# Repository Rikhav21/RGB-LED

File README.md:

# RGB-LED

## About
This is basically my attempt at making an RGB LED. I hope that I will get at least one red, green, nad blue LED,(If not I have a few), and I wat to try to turn on each LED witha  button, so that I can change the combination of the LEDs on, so tha I can make any color, and I also added a potentiameter, for the intensity for overall brightness, however I would add a poteniameter for each LEDm so that you can make any color. 
## BOM
- LED 1 Red, 1 Blue, and 1 green
- 3 220 Ohm resistors
- 1 PCB
- 3 push buttons
- 1 potentiameter
## Images

## Slack ID
U083L25T929

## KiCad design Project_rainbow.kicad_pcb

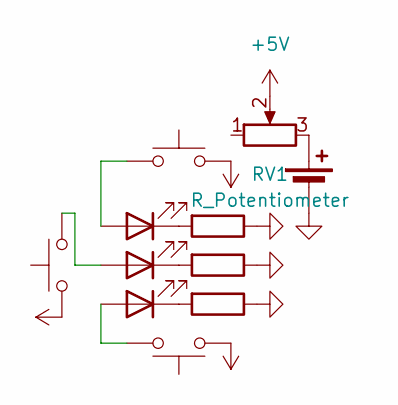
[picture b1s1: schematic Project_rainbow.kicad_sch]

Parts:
BT1: Battery_Cell; BatteryHolder_Keystone_3034_1x20mm
D1, D2, D3: LED; LED_D5.0mm
R1, R2, R3: R; R_Axial_DIN0207_L6.3mm_D2.5mm_P7.62mm_Horizontal
RV1: R_Potentiometer; Potentiometer_Vishay_T73YP_Vertical
SW4, SW5, SW6: SW_Push; SW_PUSH_6mm

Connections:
+5V: RV1.2, SW4.1, SW5.1, SW6.2
GND: BT1.2 (-), R1.1, R2.1, R3.1
unnamed: BT1.1 (+), RV1.3
unnamed: D1.2 (A), SW4.2
unnamed: D1.1 (K), R3.2
unnamed: D2.2 (A), SW5.2
unnamed: D2.1 (K), R2.2
unnamed: D3.2 (A), SW6.1
unnamed: D3.1 (K), R1.2

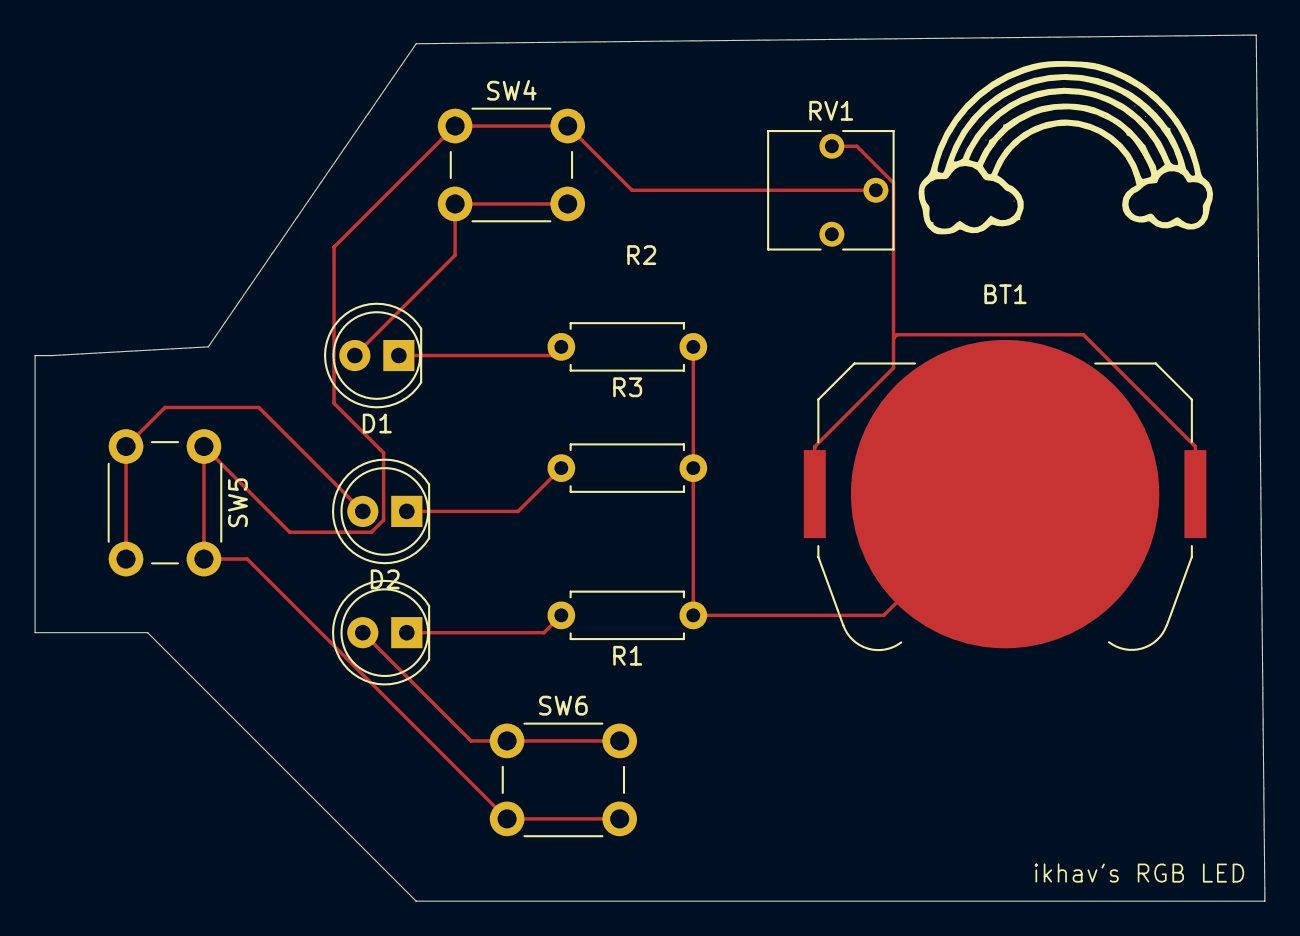
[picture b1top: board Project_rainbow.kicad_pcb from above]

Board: 2 copper layers, 71.0 x 50.0 mm, 11 parts (0 on the bottom side), 9 nets.
